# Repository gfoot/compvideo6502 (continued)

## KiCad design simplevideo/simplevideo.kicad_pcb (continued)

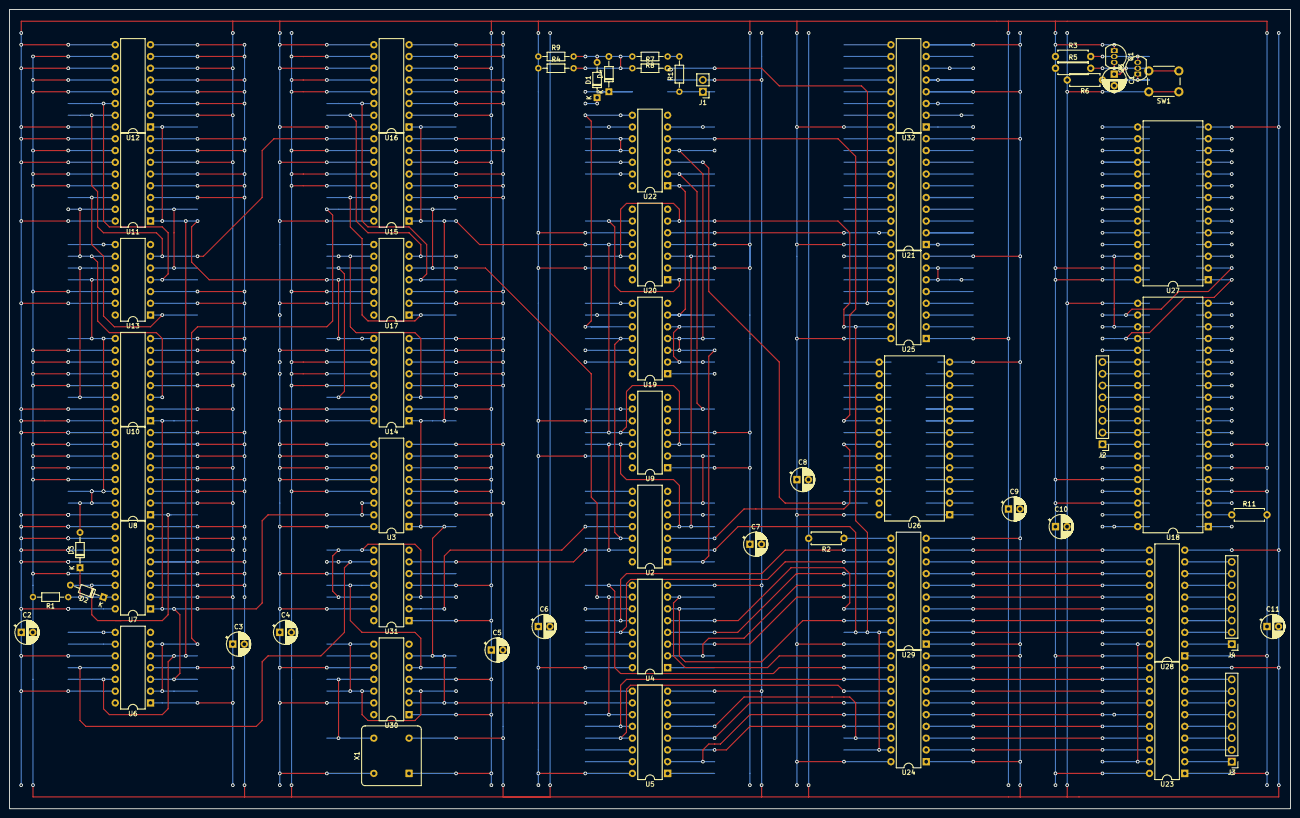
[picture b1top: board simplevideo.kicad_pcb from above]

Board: 4 copper layers, 276.9 x 172.7 mm, 65 parts (0 on the bottom side), 118 nets.

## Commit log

2020-06-09 Baseline
2020-06-10 Include 6502, ROM, etc in circuit, all laid out together
2020-06-12 New address decoding scheme and complete breadboard layout, should be ready to build
2020-06-12 Minor edits
2020-06-13 Add images of v1 results
2020-06-21 Fixed various issues discovered during building and testing
2020-09-17 Moved timing diagrams to separate schematic sheet; included PDF of schematics
2020-09-17 Add schematic thumbnail; update README.md
